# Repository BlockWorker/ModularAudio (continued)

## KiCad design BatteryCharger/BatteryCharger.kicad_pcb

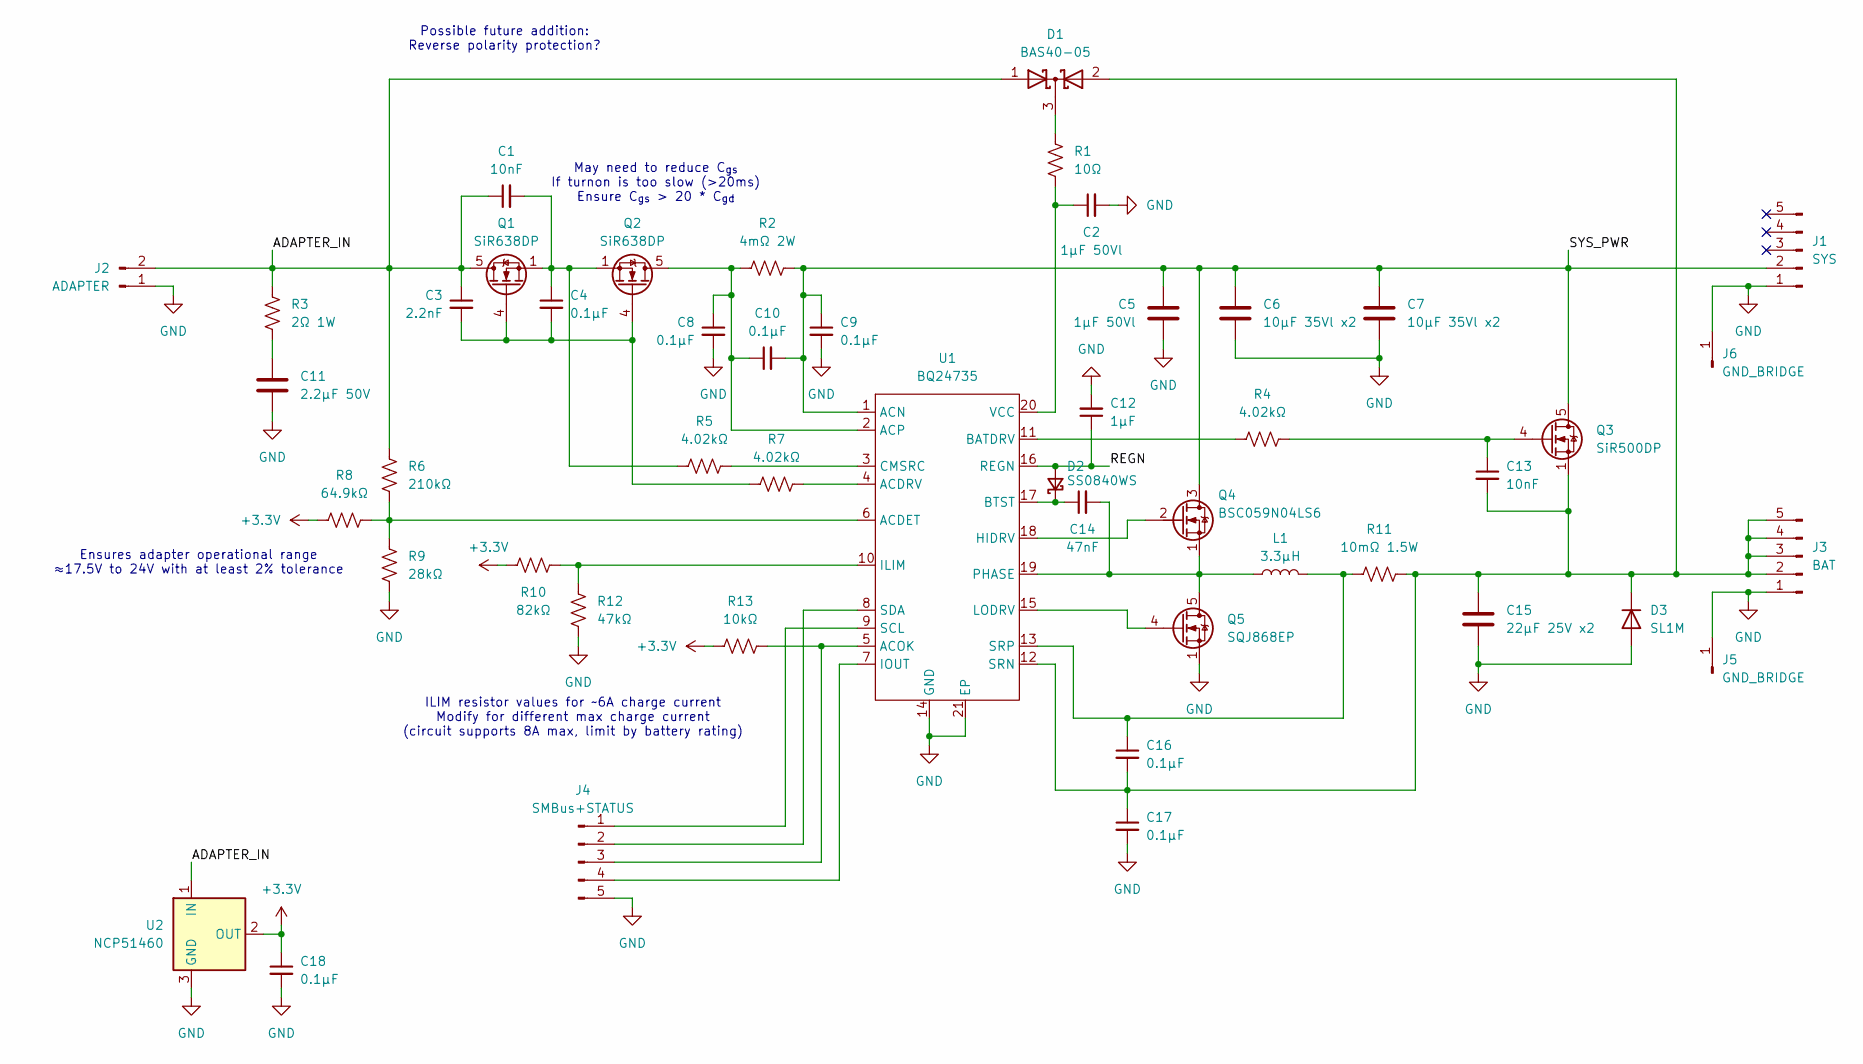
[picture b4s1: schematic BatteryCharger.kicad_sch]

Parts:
C1, C13: 10nF; C_0603_1608Metric
C2, C5: 1µF 50Vl; C_0805_2012Metric
C3: 2.2nF; C_0603_1608Metric
C4, C8, C9, C10, C16, C17, C18: 0.1µF; C_0603_1608Metric
C6, C7: 10µF 35Vl x2; C_1210_3225Metric
C11: 2.2µF 50V; C_0805_2012Metric
C12: 1µF; C_0603_1608Metric
C14: 47nF; C_0603_1608Metric
C15: 22µF 25V x2; C_1210_3225Metric
D1: BAS40-05; SOT-23
D2: SS0840WS; D_SOD-323_HandSoldering
D3: SL1M; D_SOD-123F
J1: SYS; TE_2042274_Solder
J2: ADAPTER; Molex_Mini-Fit_Max_2P_V_215915-1002
J3: BAT; TE_2042274_Solder
J4: SMBus+STATUS; Amphenol_MINITEK_WTB_1.25_5P
J5, J6: GND_BRIDGE; HolePad_2.5mm_3.5mm
L1: 3.3µH; L_Eaton_EXL1V0703
Q1, Q2: SiR638DP; PowerPAK_SO-8_Single
Q3: SiR500DP; PowerPAK_SO-8_Single
Q4: BSC059N04LS6; Infineon_PG-TDSON-8FL_6.15x5.15mm
Q5: SQJ868EP; PowerPAK_SO-8L_Single_Improved
R1: 10Ω; R_0603_1608Metric
R2: 4mΩ 2W; R_0612_1632Metric
R3: 2Ω 1W; R_0508_1220Metric
R4, R5, R7: 4.02kΩ; R_0603_1608Metric
R6: 210kΩ; R_0603_1608Metric
R8: 64.9kΩ; R_0603_1608Metric
R9: 28kΩ; R_0603_1608Metric
R10: 82kΩ; R_0603_1608Metric
R11: 10mΩ 1.5W; R_0612_1632Metric
R12: 47kΩ; R_0603_1608Metric
R13: 10kΩ; R_0603_1608Metric
U1: BQ24735; VQFN-20-1EP_3.5x3.5mm_P0.5mm_EP2.05x2.05mm
U2: NCP51460; SOT-23

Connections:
+3.3V: C18.1, R8.1, R10.1, R13.1, U2.2 (OUT)
/ADAPTER_IN: C1.1, C3.1, D1.1 (A), J2.2, Q1.5 (D), R3.1, R6.1, U2.1 (IN)
/REGN: C12.1, D2.2 (A), U1.16 (REGN)
/SYS_PWR: C5.1, C6.1, C7.1, C9.1, C10.2, J1.2, Q3.5 (D), Q4.3 (D), R2.2, U1.1 (ACN)
GND: C2.2, C5.2, C6.2, C7.2, C8.2, C9.2, C11.2, C12.2, C15.2, C17.2, C18.2, D3.2 (A), J1.1, J2.1, J3.1, J4.5, J5.1, J6.1, Q5.1 (S), Q5.2 (S), Q5.3 (S), R9.2, R12.1, U1.14 (GND), U1.21 (EP), U2.3 (GND)
unnamed: C1.2, C4.1, Q1.1 (S), Q1.2 (S), Q1.3 (S), Q2.1 (S), Q2.2 (S), Q2.3 (S), R5.1
unnamed: C11.1, R3.2
unnamed: D1.3 (K), R1.1
unnamed: C14.1, D2.1 (K), U1.17 (BTST)
unnamed: C13.2, C15.1, C16.2, C17.1, D1.2 (A), D3.1 (K), J3.2, J3.3, J3.4, J3.5, Q3.1 (S), Q3.2 (S), Q3.3 (S), R11.2, U1.12 (SRN)
unnamed: J4.1, U1.9 (SCL)
unnamed: J4.2, U1.8 (SDA)
unnamed: J4.3, R13.2, U1.5 (ACOK)
unnamed: J4.4, U1.7 (IOUT)
unnamed: C3.2, C4.2, Q1.4 (G), Q2.4 (G), R7.1
unnamed: C8.1, C10.1, Q2.5 (D), R2.1, U1.2 (ACP)
unnamed: C13.1, Q3.4 (G), R4.2
unnamed: Q4.2 (G), U1.18 (HIDRV)
unnamed: C14.2, L1.1, Q4.1 (S), Q5.5 (D), U1.19 (PHASE)
unnamed: Q5.4 (G), U1.15 (LODRV)
unnamed: R6.2, R8.2, R9.1, U1.6 (ACDET)
unnamed: R7.2, U1.4 (ACDRV)
unnamed: R4.1, U1.11 (BATDRV)
unnamed: R5.2, U1.3 (CMSRC)
unnamed: R10.2, R12.2, U1.10 (ILIM)
unnamed: C16.1, L1.2, R11.1, U1.13 (SRP)
unnamed: C2.1, R1.2, U1.20 (VCC)

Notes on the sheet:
ILIM resistor values for ~6A charge current Modify for different max charge current (circuit supports 8A max, limit by battery rating)
May need to reduce C_{gs} If turnon is too slow (>20ms) Ensure C_{gs} > 20 * C_{gd}
Possible future addition: Reverse polarity protection?
Ensures adapter operational range ≈17.5V to 24V with at least 2% tolerance

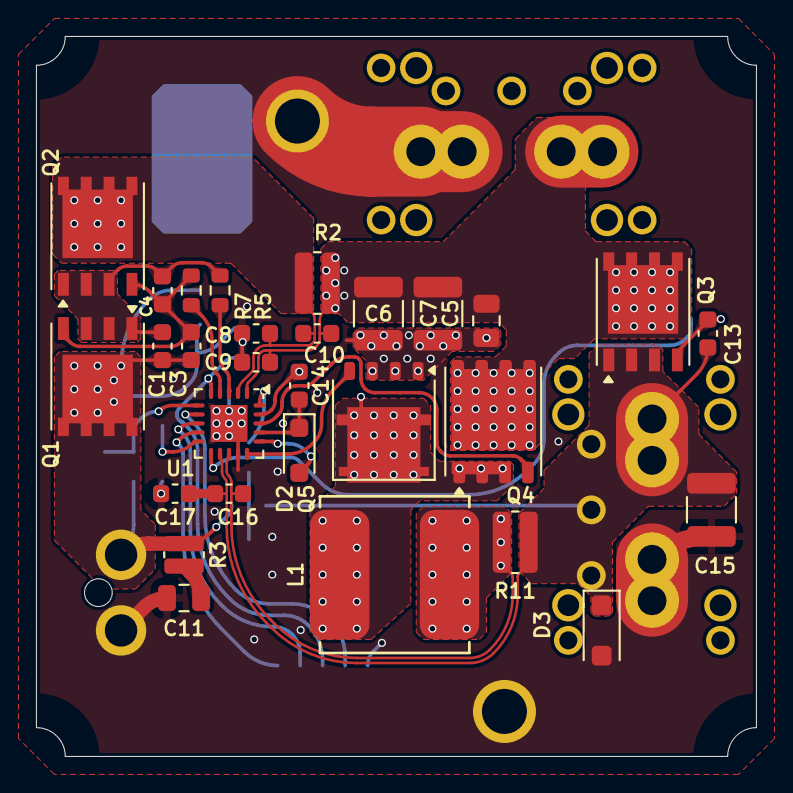
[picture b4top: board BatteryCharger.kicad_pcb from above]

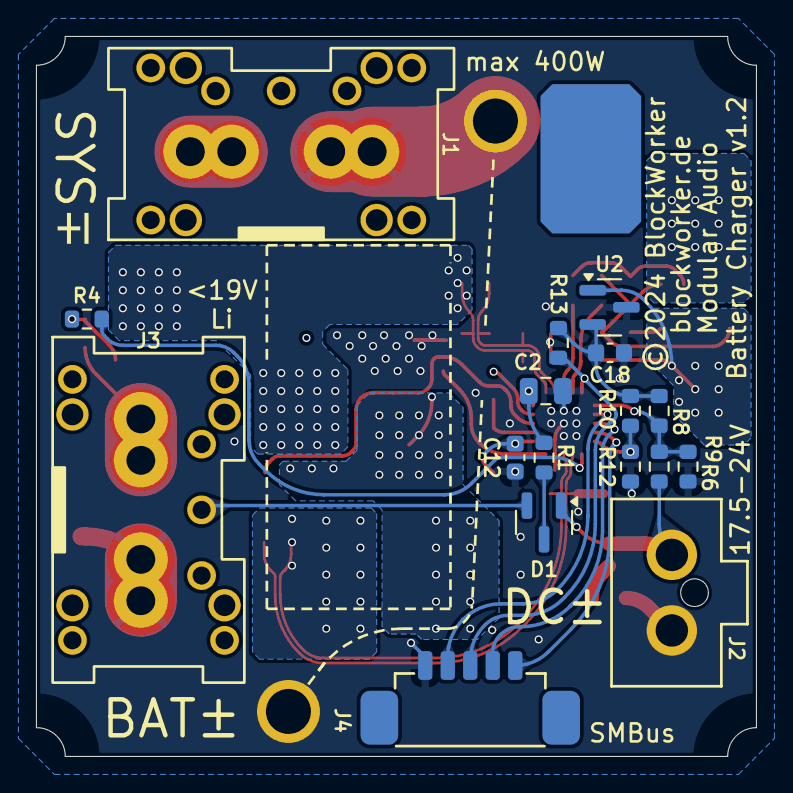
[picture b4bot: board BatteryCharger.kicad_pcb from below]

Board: 4 copper layers, 40.0 x 40.0 mm, 48 parts (17 on the bottom side), 27 nets.

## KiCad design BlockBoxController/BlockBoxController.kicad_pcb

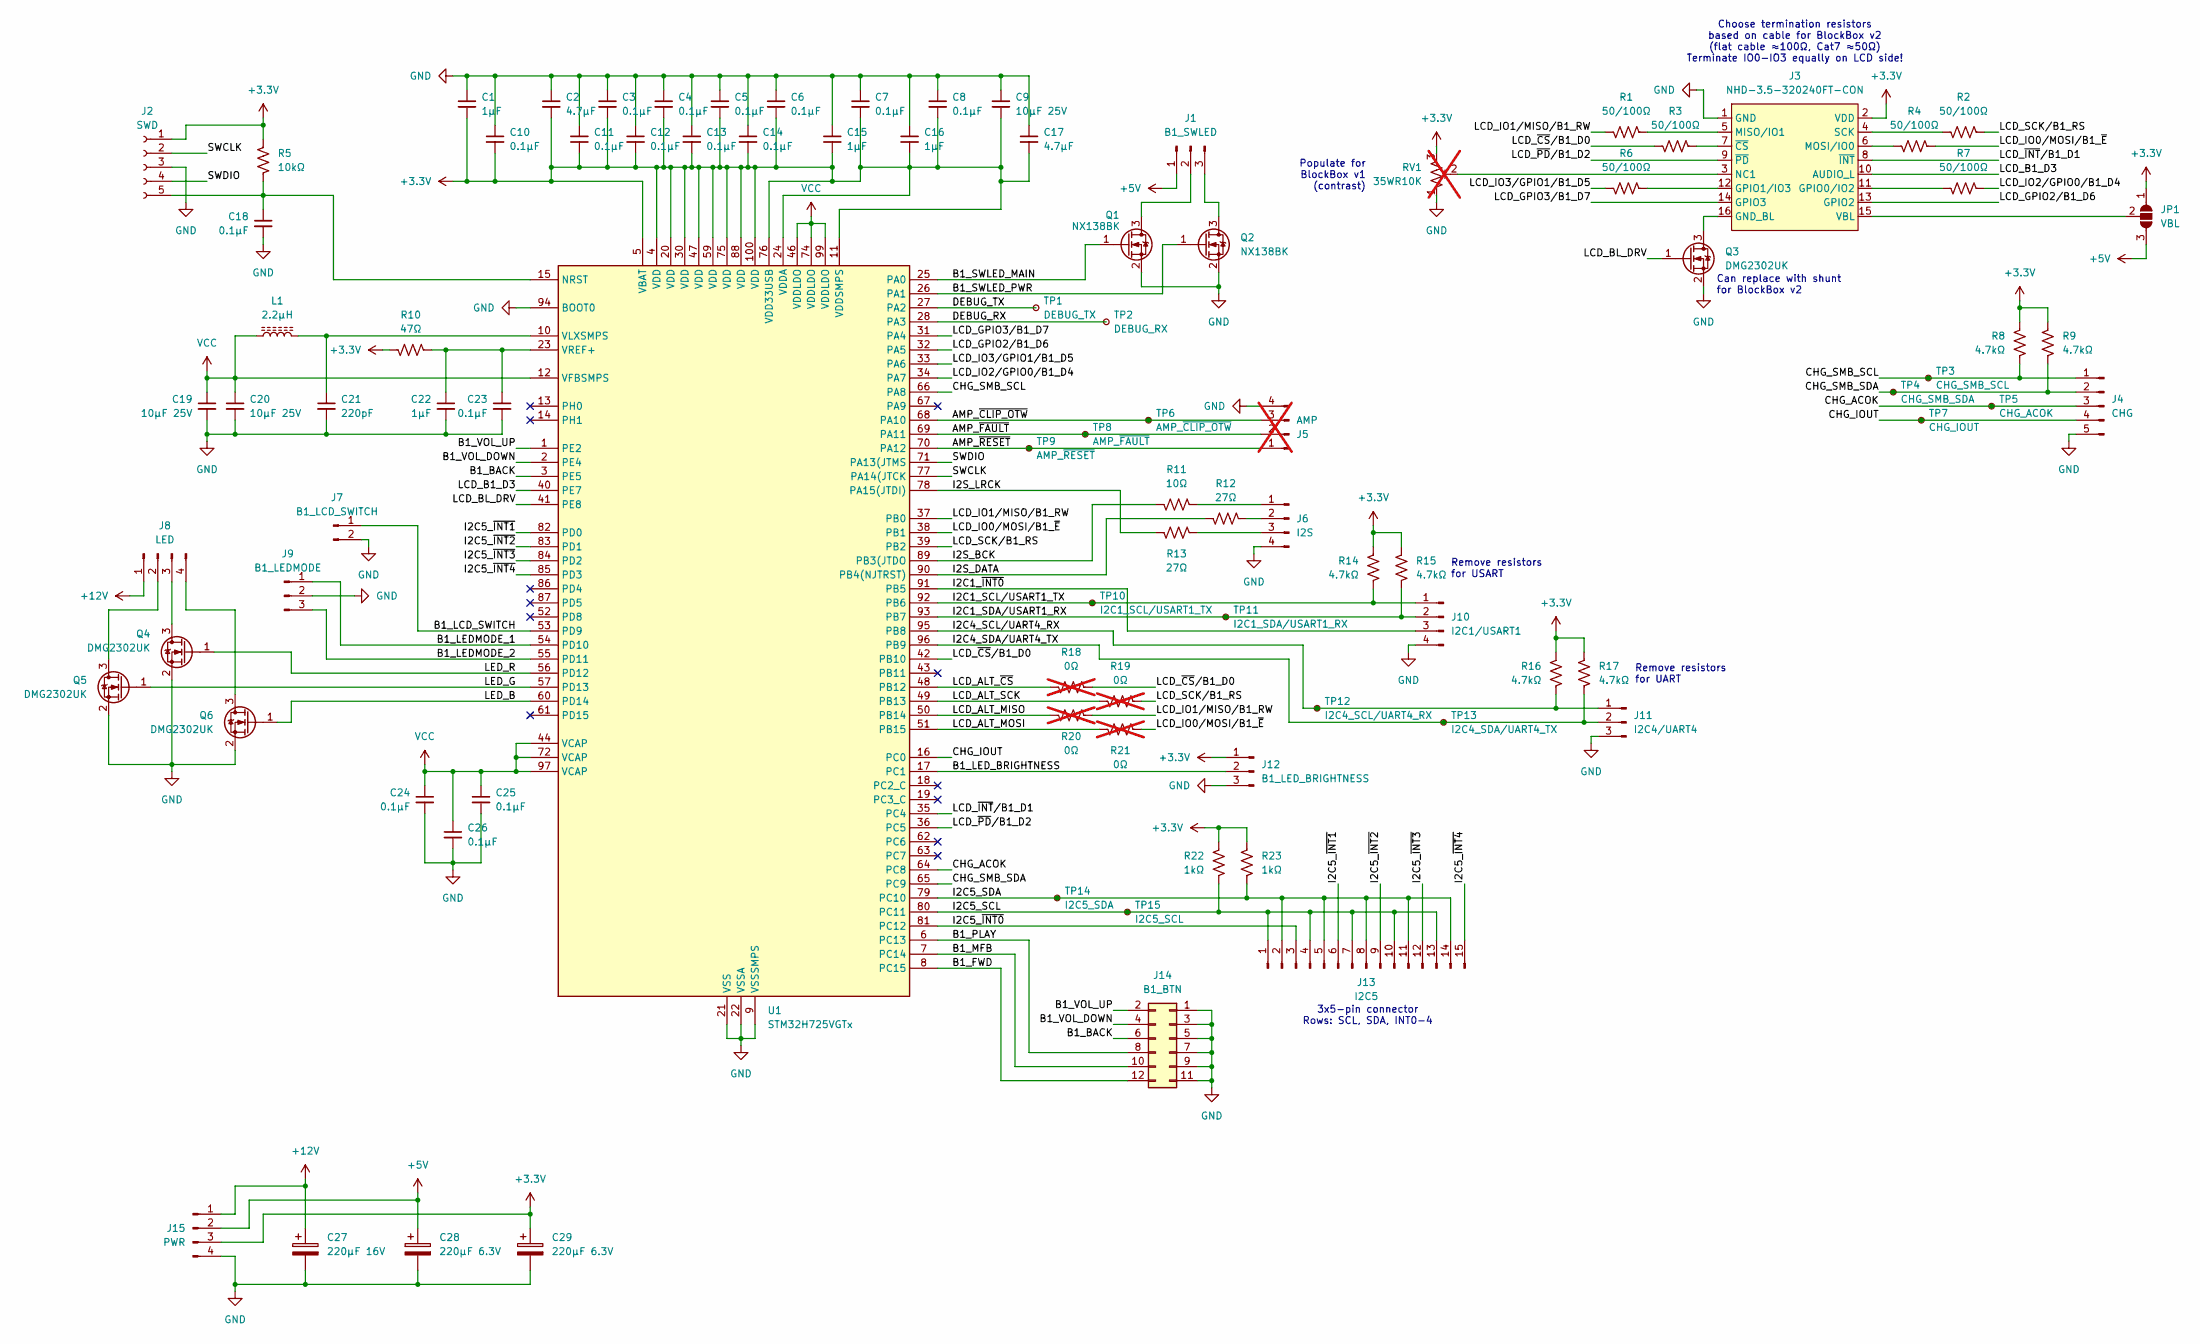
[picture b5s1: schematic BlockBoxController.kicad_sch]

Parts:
C1, C15, C16, C22: 1µF; C_0603_1608Metric
C2, C17: 4.7µF; C_0603_1608Metric
C3, C4, C5, C6, C7, C8, C10, C11, C12, C13, C14, C18, C23, C24, C25, C26: 0.1µF; C_0603_1608Metric
C9, C19, C20: 10µF 25V; C_0805_2012Metric
C21: 220pF; C_0603_1608Metric
C27: 220µF 16V; CP_Elec_6.3x7.7
C28, C29: 220µF 6.3V; CP_Elec_5x5.8
J1: B1_SWLED; PinHeader_1x03_P2.54mm_Vertical
J2: SWD; PinSocket_1x05_P1.27mm_Vertical_SMD_Pin1Right
J3: NHD-3.5-320240FT-CON; PinHeader_2x09_P2.54mm_Vertical_Mirrored
J4: CHG; Amphenol_MINITEK_WTB_1.25_5P
J5: AMP; Amphenol_MINITEK_WTB_1.25_4P; not fitted
J6: I2S; Amphenol_MINITEK_WTB_1.25_4P
J7: B1_LCD_SWITCH; PinHeader_1x02_P2.54mm_Vertical
J8: LED; PinHeader_1x04_P2.54mm_Vertical
J9: B1_LEDMODE; PinHeader_1x03_P2.54mm_Vertical
J10: I2C1/USART1; Amphenol_MINITEK_WTB_1.25_4P
J11: I2C4/UART4; Amphenol_MINITEK_WTB_1.25_3P
J12: B1_LED_BRIGHTNESS; PinHeader_1x03_P2.54mm_Vertical
J13: I2C5; PinHeader_3x05_P2.54mm_Vertical
J14: B1_BTN; PinHeader_2x06_P2.54mm_Vertical
J15: PWR; Molex_Nano-Fit_105309-xx04_1x04_P2.50mm_Vertical
JP1: VBL; SolderJumper-3_P1.3mm_Open_RoundedPad1.0x1.5mm
L1: 2.2µH; L_0805_2012Metric
Q1, Q2: NX138BK; SOT-23
Q3, Q4, Q5, Q6: DMG2302UK; SOT-23
R1, R2, R3, R4, R6, R7: 50/100Ω; R_0603_1608Metric
R5: 10kΩ; R_0603_1608Metric
R8, R9, R14, R15, R16, R17: 4.7kΩ; R_0603_1608Metric
R10: 47Ω; R_0603_1608Metric
R11: 10Ω; R_0603_1608Metric
R12, R13: 27Ω; R_0603_1608Metric
R18, R19, R20, R21: 0Ω; R_0603_1608Metric; not fitted
R22, R23: 1kΩ; R_0603_1608Metric
RV1: 35WR10K; Potentiometer_TT_35W; not fitted
TP1: DEBUG_TX; TP_0603_1608Metric_Fused
TP2: DEBUG_RX; TP_0603_1608Metric_Fused
TP3: CHG_SMB_SCL; TP_0603_1608Metric_Fused
TP4: CHG_SMB_SDA; TP_0603_1608Metric_Fused
TP5: CHG_ACOK; TP_0603_1608Metric_Fused
TP6: AMP_~{CLIP_OTW}; TestPoint_Pad_D1.0mm
TP7: CHG_IOUT; TestPoint_Pad_D1.0mm
TP8: AMP_~{FAULT}; TestPoint_Pad_D1.0mm
TP9: AMP_~{RESET}; TestPoint_Pad_D1.0mm
TP10: I2C1_SCL/USART1_TX; TP_0603_1608Metric_Fused
TP11: I2C1_SDA/USART1_RX; TP_0603_1608Metric_Fused
TP12: I2C4_SCL/UART4_RX; TP_0603_1608Metric_Fused
TP13: I2C4_SDA/UART4_TX; TP_0603_1608Metric_Fused
TP14: I2C5_SDA; TP_0603_1608Metric_Fused
TP15: I2C5_SCL; TP_0603_1608Metric_Fused
U1: STM32H725VGTx; LQFP-100_14x14mm_P0.5mm

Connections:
+3.3V: C1.2, C2.2, C3.2, C4.2, C5.2, C6.2, C7.2, C8.2, C9.2, C10.2, C11.2, C12.2, C13.2, C14.2, C15.2, C16.2, C17.2, C29.1, J2.1, J3.2 (VDD), J12.1, J15.3, JP1.1 (A), R5.1, R8.1, R9.1, R10.1, R14.1, R15.1, R16.1, R17.1, R22.1, R23.1, RV1.3, U1.4 (VDD), U1.5 (VBAT), U1.11 (VDDSMPS), U1.20 (VDD), U1.24 (VDDA), U1.30 (VDD), U1.47 (VDD), U1.59 (VDD), U1.75 (VDD), U1.76 (VDD33USB), U1.88 (VDD), U1.100 (VDD)
+5V: C28.1, J1.1, J15.2, JP1.3 (B)
+12V: C27.1, J8.1, J15.1
/AMP_~CLIP_OTW: J5.3, TP6.1, U1.68 (PA10)
/AMP_~FAULT: J5.2, TP8.1, U1.69 (PA11)
/AMP_~RESET: J5.1, TP9.1, U1.70 (PA12)
/B1_BACK: J14.6, U1.3 (PE5)
/B1_FWD: J14.12, U1.8 (PC15)
/B1_LCD_SWITCH: J7.1, U1.53 (PD9)
/B1_LEDMODE_1: J9.1, U1.54 (PD10)
/B1_LEDMODE_2: J9.3, U1.55 (PD11)
/B1_LED_BRIGHTNESS: J12.2, U1.17 (PC1)
/B1_MFB: J14.10, U1.7 (PC14)
/B1_PLAY: J14.8, U1.6 (PC13)
/B1_SWLED_MAIN: Q1.1 (G), U1.25 (PA0)
/B1_SWLED_PWR: Q2.1 (G), U1.26 (PA1)
/B1_VOL_DOWN: J14.4, U1.2 (PE4)
/B1_VOL_UP: J14.2, U1.1 (PE2)
/CHG_ACOK: J4.3, TP5.1, U1.64 (PC8)
/CHG_IOUT: J4.4, TP7.1, U1.16 (PC0)
/CHG_SMB_SCL: J4.1, R8.2, TP3.1, U1.66 (PA8)
/CHG_SMB_SDA: J4.2, R9.2, TP4.1, U1.65 (PC9)
/DEBUG_RX: TP2.1, U1.28 (PA3)
/DEBUG_TX: TP1.1, U1.27 (PA2)
/I2C1_SCL/USART1_TX: J10.1, R14.2, TP10.1, U1.92 (PB6)
/I2C1_SDA/USART1_RX: J10.2, R15.2, TP11.1, U1.93 (PB7)
/I2C1_~INT0: J10.3, U1.91 (PB5)
/I2C4_SCL/UART4_RX: J11.1, R16.2, TP12.1, U1.95 (PB8)
/I2C4_SDA/UART4_TX: J11.2, R17.2, TP13.1, U1.96 (PB9)
/I2C5_SCL: J13.1, J13.4, J13.7, J13.10, J13.13, R22.2, TP15.1, U1.80 (PC11)
/I2C5_SDA: J13.2, J13.5, J13.8, J13.11, J13.14, R23.2, TP14.1, U1.79 (PC10)
/I2C5_~INT0: J13.3, U1.81 (PC12)
/I2C5_~INT1: J13.6, U1.82 (PD0)
/I2C5_~INT2: J13.9, U1.83 (PD1)
/I2C5_~INT3: J13.12, U1.84 (PD2)
/I2C5_~INT4: J13.15, U1.85 (PD3)
/I2S_BCK: R11.1, U1.89 (PB3(JTDO)
/I2S_DATA: R12.1, U1.90 (PB4(NJTRST))
/I2S_LRCK: R13.1, U1.78 (PA15(JTDI))
/LCD_ALT_MISO: R20.1, U1.50 (PB14)
/LCD_ALT_MOSI: R21.1, U1.51 (PB15)
/LCD_ALT_SCK: R19.1, U1.49 (PB13)
/LCD_ALT_~CS: R18.1, U1.48 (PB12)
/LCD_B1_D3: J3.10 (AUDIO_L), U1.40 (PE7)
/LCD_BL_DRV: Q3.1 (G), U1.41 (PE8)
/LCD_GPIO2/B1_D6: J3.13 (GPIO2), U1.32 (PA5)
/LCD_GPIO3/B1_D7: J3.14 (GPIO3), U1.31 (PA4)
/LCD_IO0/MOSI/B1_~E: R4.2, R21.2, U1.38 (PB1)
/LCD_IO1/MISO/B1_RW: R1.1, R20.2, U1.37 (PB0)
/LCD_IO2/GPIO0/B1_D4: R7.2, U1.34 (PA7)
/LCD_IO3/GPIO1/B1_D5: R6.1, U1.33 (PA6)
/LCD_SCK/B1_RS: R2.2, R19.2, U1.39 (PB2)
/LCD_~CS/B1_D0: R3.1, R18.2, U1.42 (PB10)
/LCD_~INT/B1_D1: J3.8 (~INT), U1.35 (PC4)
/LCD_~PD/B1_D2: J3.9 (~PD), U1.36 (PC5)
/LED_B: Q6.1 (G), U1.60 (PD14)
/LED_G: Q5.1 (G), U1.57 (PD13)
/LED_R: Q4.1 (G), U1.56 (PD12)
/SWCLK: J2.2, U1.77 (PA14(JTCK)
/SWDIO: J2.4, U1.71 (PA13(JTMS)
GND: C1.1, C2.1, C3.1, C4.1, C5.1, C6.1, C7.1, C8.1, C9.1, C10.1, C11.1, C12.1, C13.1, C14.1, C15.1, C16.1, C17.1, C18.2, C19.2, C20.2, C21.2, C22.2, C23.2, C24.2, C25.2, C26.2, C27.2, C28.2, C29.2, J2.3, J3.1 (GND), J4.5, J5.4, J6.4, J7.2, J9.2, J10.4, J11.3, J12.3, J14.1, J14.3, J14.5, J14.7, J14.9, J14.11, J15.4, Q1.2 (S), Q2.2 (S), Q3.2 (S), Q4.2 (S), Q5.2 (S), Q6.2 (S), RV1.1, U1.9 (VSSSMPS), U1.21 (VSS), U1.22 (VSSA), U1.29 (VSS), U1.45 (VSS), U1.58 (VSS), U1.73 (VSS), U1.94 (BOOT0), U1.98 (VSS)
unnamed: J1.2, Q1.3 (D)
unnamed: J1.3, Q2.3 (D)
unnamed: C18.1, J2.5, R5.2, U1.15 (NRST)
unnamed: J3.11 (GPIO0/IO2), R7.1
unnamed: J3.12 (GPIO1/IO3), R6.2
unnamed: J3.5 (MISO/IO1), R1.2
unnamed: J3.6 (MOSI/IO0), R4.1
unnamed: J3.3 (NC1), RV1.2
unnamed: J3.4 (SCK), R2.1
unnamed: J3.7 (~CS), R3.2
unnamed: J6.1, R11.2
unnamed: J6.2, R12.2
unnamed: J6.3, R13.2
unnamed: J8.2, Q5.3 (D)
unnamed: J8.3, Q4.3 (D)
unnamed: J8.4, Q6.3 (D)
unnamed: J3.15 (VBL), J3.17 (VBL), JP1.2 (C)
unnamed: J3.16 (GND_BL), J3.18 (GND_BL), Q3.3 (D)
unnamed: C21.1, L1.2, U1.10 (VLXSMPS)
unnamed: C22.1, C23.1, R10.2, U1.23 (VREF+)
VCC: C19.1, C20.1, C24.1, C25.1, C26.1, L1.1, U1.12 (VFBSMPS), U1.44 (VCAP), U1.46 (VDDLDO), U1.72 (VCAP), U1.74 (VDDLDO), U1.97 (VCAP), U1.99 (VDDLDO)

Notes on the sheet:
Can replace with shunt for BlockBox v2
3x5-pin connector Rows: SCL, SDA, INT0-4
Remove resistors for UART
Populate for BlockBox v1 (contrast)
Choose termination resistors based on cable for BlockBox v2 (flat cable ≈100Ω, Cat7 ≈50Ω) Terminate IO0-IO3 equally on LCD side!
Remove resistors for USART

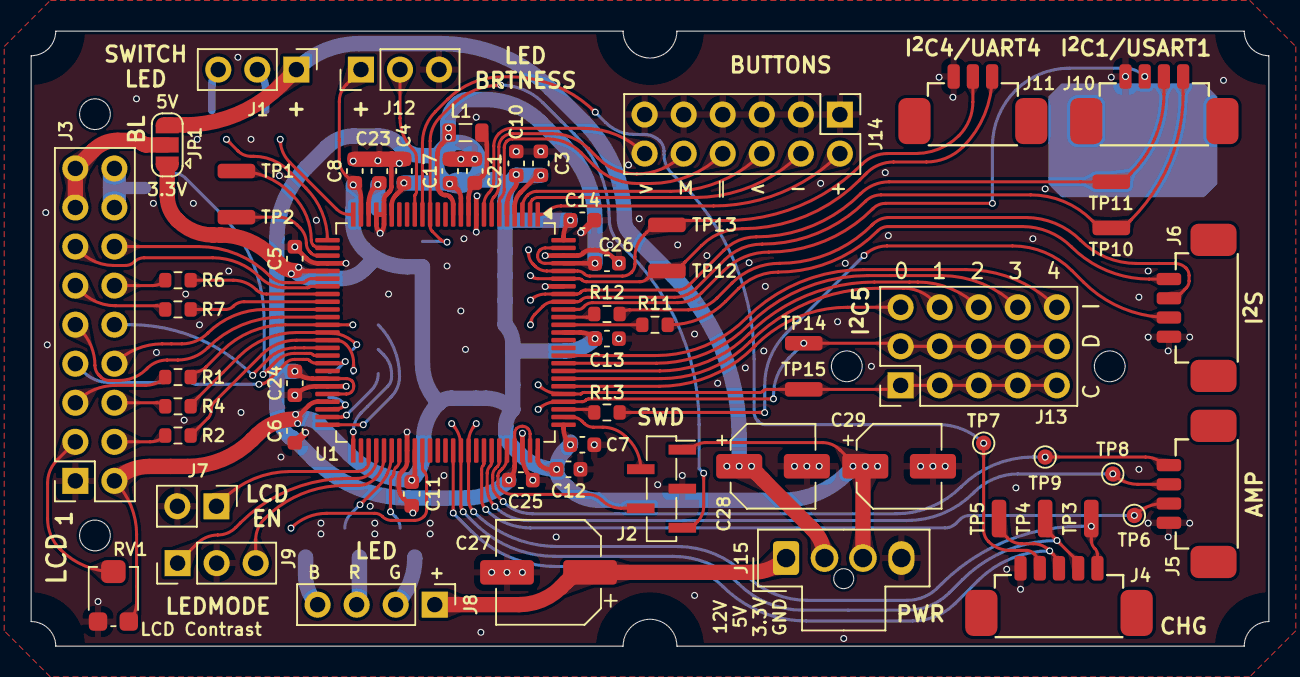
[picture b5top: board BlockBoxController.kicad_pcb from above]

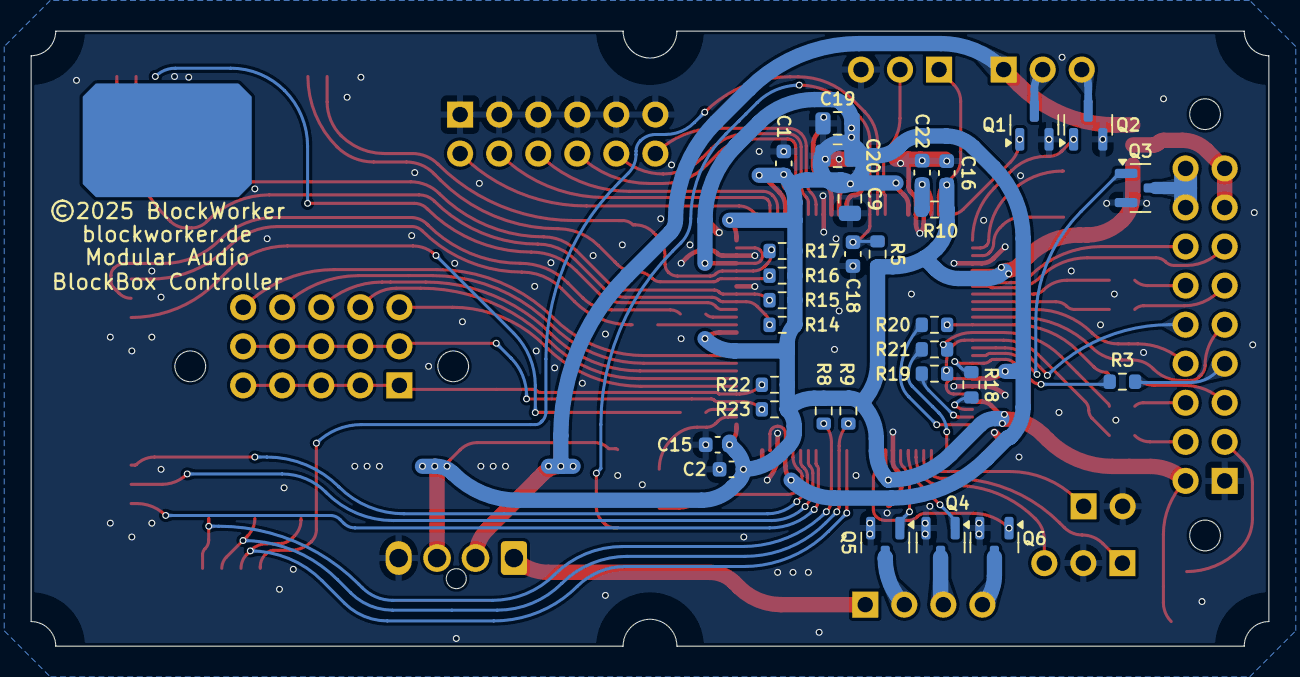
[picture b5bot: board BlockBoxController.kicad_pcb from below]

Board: 4 copper layers, 80.5 x 40.0 mm, 92 parts (30 on the bottom side), 82 nets.

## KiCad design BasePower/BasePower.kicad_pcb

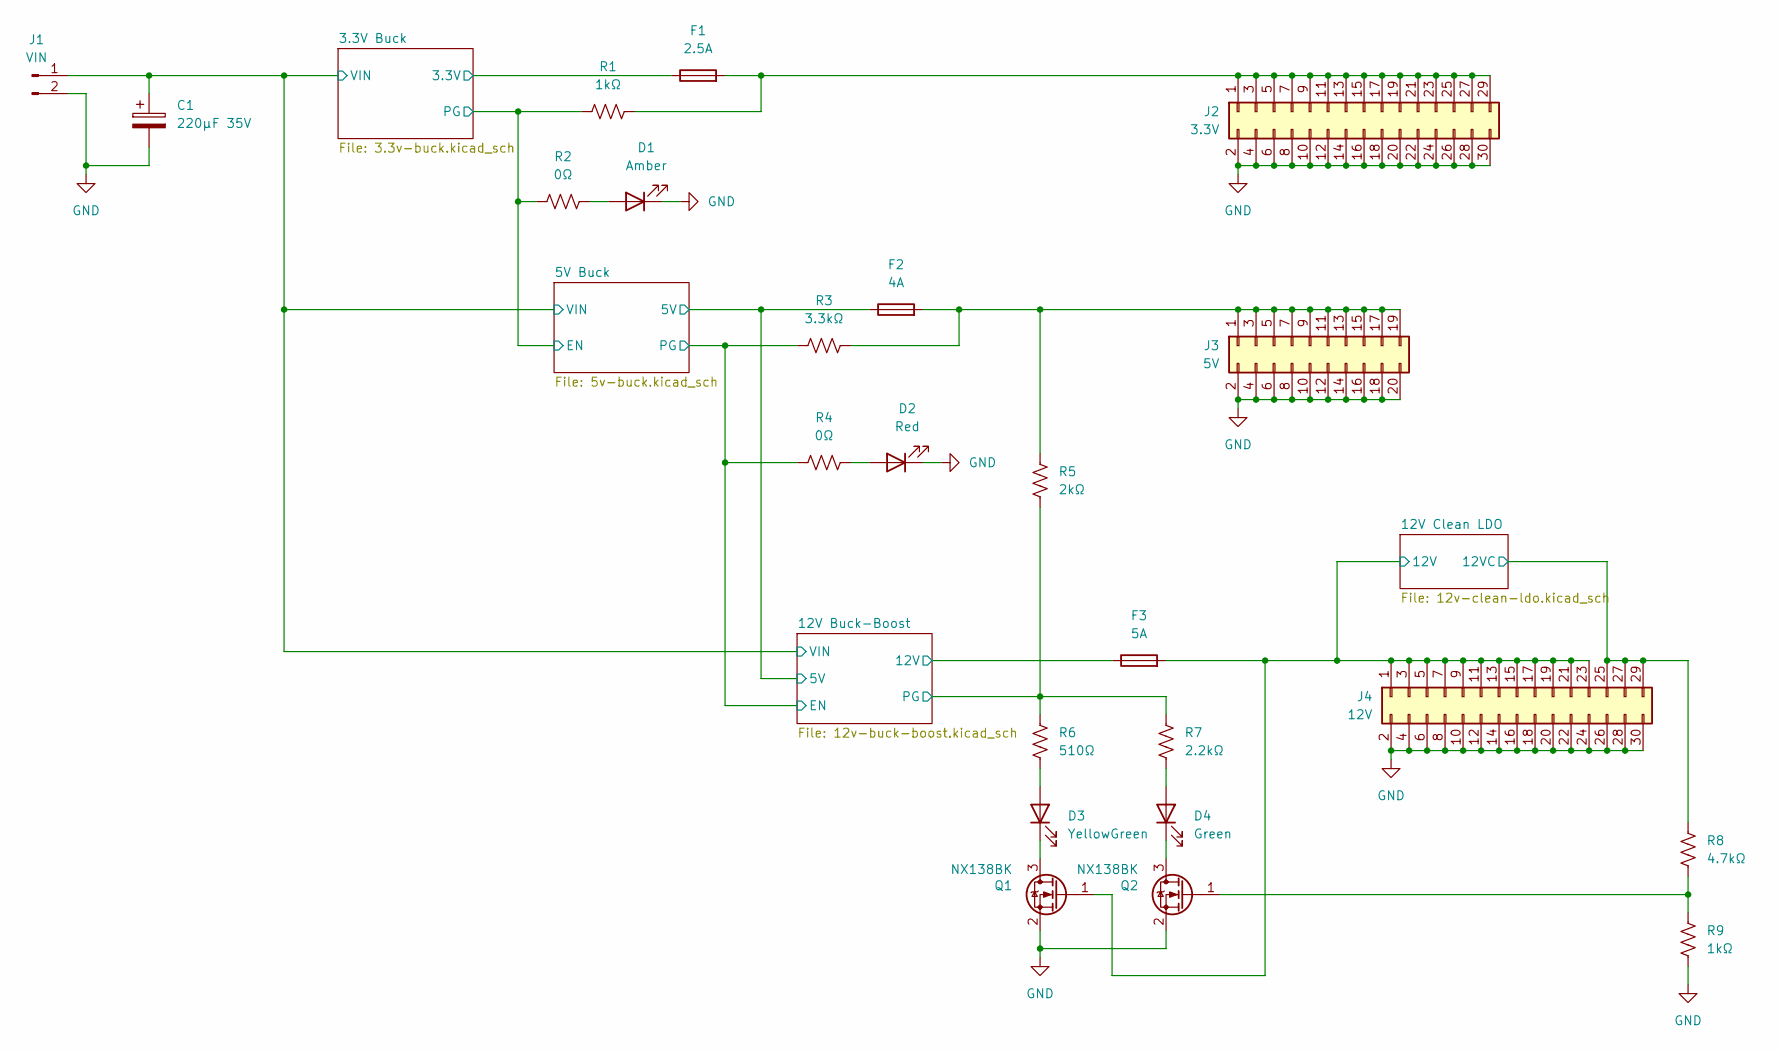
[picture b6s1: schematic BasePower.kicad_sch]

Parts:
C1: 220µF 35V; CP_Radial_D8.0mm_P3.50mm
D1: Amber; LED_0603_1608Metric
D2: Red; LED_0603_1608Metric
D3: YellowGreen; LED_0603_1608Metric
D4: Green; LED_0603_1608Metric
F1: 2.5A; Fuse_0603_1608Metric
F2: 4A; Fuse_0603_1608Metric
F3: 5A; Fuse_0603_1608Metric
J1: VIN; Molex_Nano-Fit_105309-xx02_1x02_P2.50mm_Vertical
J2: 3.3V; PinHeader_2x15_P2.54mm_Vertical
J3: 5V; PinHeader_2x10_P2.54mm_Vertical
J4: 12V; PinHeader_2x15_P2.54mm_Vertical
Q1, Q2: NX138BK; SOT-23
R1, R9: 1kΩ; R_0603_1608Metric
R2, R4: 0Ω; R_0603_1608Metric
R3: 3.3kΩ; R_0603_1608Metric
R5: 2kΩ; R_0603_1608Metric
R6: 510Ω; R_0603_1608Metric
R7: 2.2kΩ; R_0603_1608Metric
R8: 4.7kΩ; R_0603_1608Metric

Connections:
/3.3V Buck/3.3V: F1.1; also elsewhere on the board
/3.3V Buck/PG: R1.1, R2.1; also elsewhere on the board
/12V Buck-Boost/5V: F2.1; also elsewhere on the board
/12V Buck-Boost/12V: F3.1; also elsewhere on the board
/12V Buck-Boost/EN: R3.1, R4.1; also elsewhere on the board
/12V Buck-Boost/PG: R5.1, R6.1, R7.1; also elsewhere on the board
/12V Buck-Boost/VIN: C1.1, J1.1; also elsewhere on the board
/12V Clean LDO/12V: F3.2, J4.1, J4.3, J4.5, J4.7, J4.9, J4.11, J4.13, J4.15, J4.17, J4.19, J4.21, J4.23, Q1.1 (G); also elsewhere on the board
/12V Clean LDO/12VC: J4.25, J4.27, J4.29, R8.1; also elsewhere on the board
GND: C1.2, D1.1 (K), D2.1 (K), J1.2, J2.2, J2.4, J2.6, J2.8, J2.10, J2.12, J2.14, J2.16, J2.18, J2.20, J2.22, J2.24, J2.26, J2.28, J2.30, J3.2, J3.4, J3.6, J3.8, J3.10, J3.12, J3.14, J3.16, J3.18, J3.20, J4.2, J4.4, J4.6, J4.8, J4.10, J4.12, J4.14, J4.16, J4.18, J4.20, J4.22, J4.24, J4.26, J4.28, J4.30, Q1.2 (S), Q2.2 (S), R9.2; also elsewhere on the board
unnamed: D1.2 (A), R2.2
unnamed: D2.2 (A), R4.2
unnamed: D3.2 (A), R6.2
unnamed: D3.1 (K), Q1.3 (D)
unnamed: D4.2 (A), R7.2
unnamed: D4.1 (K), Q2.3 (D)
unnamed: F1.2, J2.1, J2.3, J2.5, J2.7, J2.9, J2.11, J2.13, J2.15, J2.17, J2.19, J2.21, J2.23, J2.25, J2.27, J2.29, R1.2
unnamed: F2.2, J3.1, J3.3, J3.5, J3.7, J3.9, J3.11, J3.13, J3.15, J3.17, J3.19, R3.2, R5.2
unnamed: Q2.1 (G), R8.2, R9.1

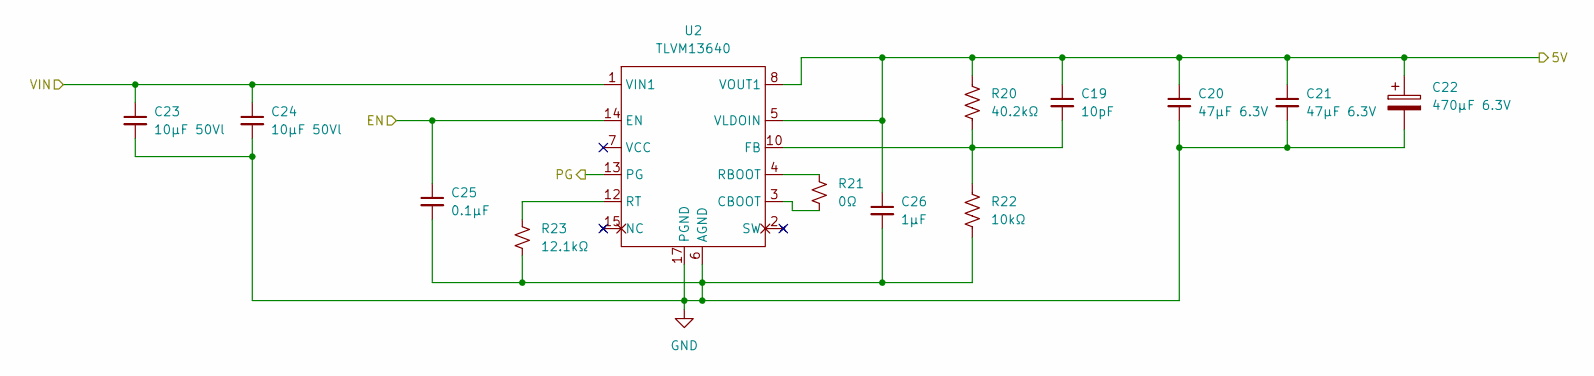
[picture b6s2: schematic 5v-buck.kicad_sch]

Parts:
C19: 10pF; C_0603_1608Metric
C20, C21: 47µF 6.3V; C_1210_3225Metric
C22: 470µF 6.3V; CP_Radial_D6.3mm_P2.50mm
C23, C24: 10µF 50Vl; C_1210_3225Metric
C25: 0.1µF; C_0603_1608Metric
C26: 1µF; C_0603_1608Metric
R20: 40.2kΩ; R_0603_1608Metric
R21: 0Ω; R_0603_1608Metric
R22: 10kΩ; R_0603_1608Metric
R23: 12.1kΩ; R_0603_1608Metric
U2: TLVM13640; TI_B3QFN-20

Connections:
/3.3V Buck/PG: C25.1, U2.14 (EN); also elsewhere on the board
/12V Buck-Boost/5V: C19.1, C20.1, C21.1, C22.1, C26.1, R20.1, U2.5 (VLDOIN), U2.8 (VOUT1), U2.9 (VOUT2); also elsewhere on the board
/12V Buck-Boost/EN: U2.13 (PG); also elsewhere on the board
/12V Buck-Boost/VIN: C23.1, C24.1, U2.1 (VIN1), U2.16 (VIN2); also elsewhere on the board
GND: C20.2, C21.2, C22.2, C23.2, C24.2, C25.2, C26.2, R22.2, R23.2, U2.6 (AGND), U2.11 (AGND), U2.17 (PGND), U2.18 (PGND), U2.19 (PGND), U2.20 (PGND); also elsewhere on the board
unnamed: R21.2, U2.3 (CBOOT)
unnamed: C19.2, R20.2, R22.1, U2.10 (FB)
unnamed: R21.1, U2.4 (RBOOT)
unnamed: R23.1, U2.12 (RT)

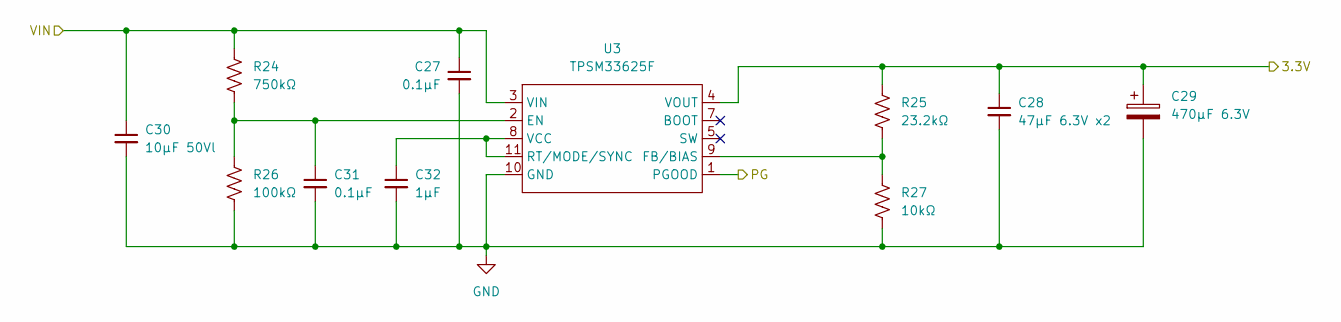
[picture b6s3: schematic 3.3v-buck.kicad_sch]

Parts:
C27, C31: 0.1µF; C_0603_1608Metric
C28: 47µF 6.3V x2; C_1210_3225Metric
C29: 470µF 6.3V; CP_Radial_D6.3mm_P2.50mm
C30: 10µF 50Vl; C_1210_3225Metric
C32: 1µF; C_0603_1608Metric
R24: 750kΩ; R_0603_1608Metric
R25: 23.2kΩ; R_0603_1608Metric
R26: 100kΩ; R_0603_1608Metric
R27: 10kΩ; R_0603_1608Metric
U3: TPSM33625F; TI_QFN-FCMOD-HR

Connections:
/3.3V Buck/3.3V: C28.1, C29.1, R25.1, U3.4 (VOUT); also elsewhere on the board
/3.3V Buck/PG: U3.1 (PGOOD); also elsewhere on the board
/12V Buck-Boost/VIN: C27.1, C30.1, R24.1, U3.3 (VIN); also elsewhere on the board
GND: C27.2, C28.2, C29.2, C30.2, C31.2, C32.2, R26.2, R27.2, U3.10 (GND); also elsewhere on the board
unnamed: C31.1, R24.2, R26.1, U3.2 (EN)
unnamed: R25.2, R27.1, U3.9 (FB/BIAS)
unnamed: C32.1, U3.8 (VCC), U3.11 (RT/MODE/SYNC)

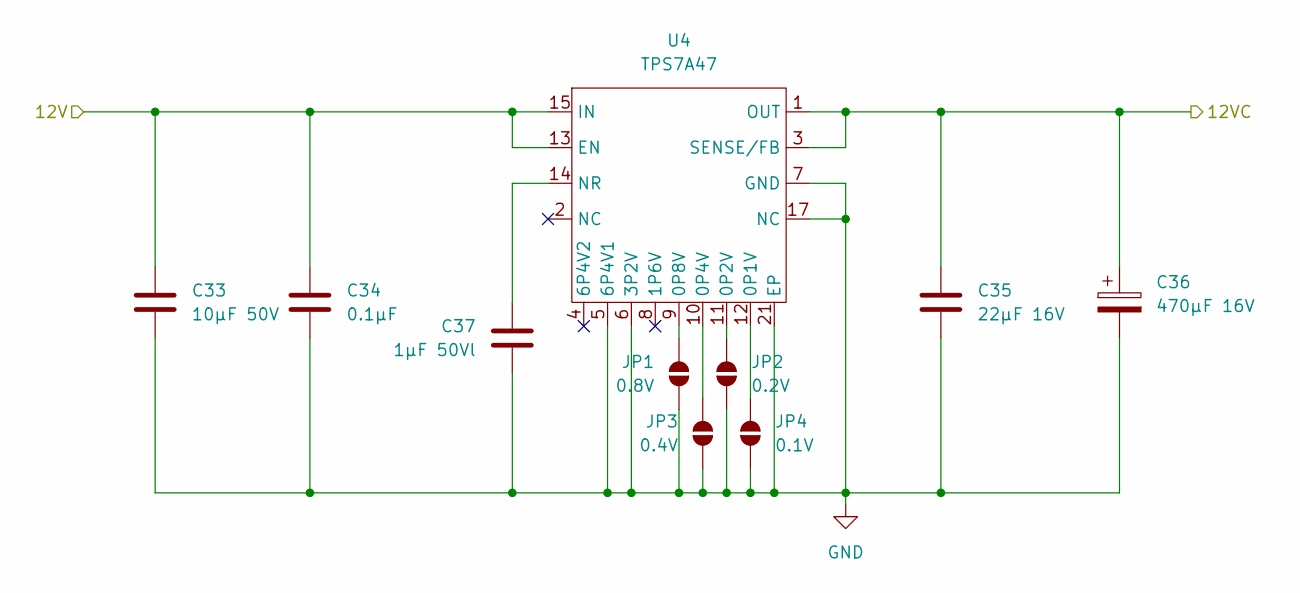
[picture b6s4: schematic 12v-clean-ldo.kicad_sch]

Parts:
C33: 10µF 50V; C_1206_3216Metric
C34: 0.1µF; C_0603_1608Metric
C35: 22µF 16V; C_1210_3225Metric
C36: 470µF 16V; CP_Radial_D6.3mm_P2.50mm
C37: 1µF 50Vl; C_0805_2012Metric
JP1: 0.8V; SolderJumper-2_P1.3mm_Open_RoundedPad1.0x1.5mm
JP2: 0.2V; SolderJumper-2_P1.3mm_Open_RoundedPad1.0x1.5mm
JP3: 0.4V; SolderJumper-2_P1.3mm_Open_RoundedPad1.0x1.5mm
JP4: 0.1V; SolderJumper-2_P1.3mm_Open_RoundedPad1.0x1.5mm
U4: TPS7A47; Texas_RGW0020A_VQFN-20-1EP_5x5mm_P0.65mm_EP3.15x3.15mm

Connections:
/12V Clean LDO/12V: C33.1, C34.1, U4.13 (EN), U4.15 (IN), U4.16 (IN); also elsewhere on the board
/12V Clean LDO/12VC: C35.1, C36.1, U4.1 (OUT), U4.3 (SENSE/FB), U4.20 (OUT); also elsewhere on the board
GND: C33.2, C34.2, C35.2, C36.2, C37.2, JP1.1 (A), JP2.1 (A), JP3.1 (A), JP4.1 (A), U4.5 (6P4V1), U4.6 (3P2V), U4.7 (GND), U4.17 (NC), U4.18 (NC), U4.19 (NC), U4.21 (EP); also elsewhere on the board
unnamed: JP1.2 (B), U4.9 (0P8V)
unnamed: JP2.2 (B), U4.11 (0P2V)
unnamed: JP3.2 (B), U4.10 (0P4V)
unnamed: JP4.2 (B), U4.12 (0P1V)
unnamed: C37.1, U4.14 (NR)

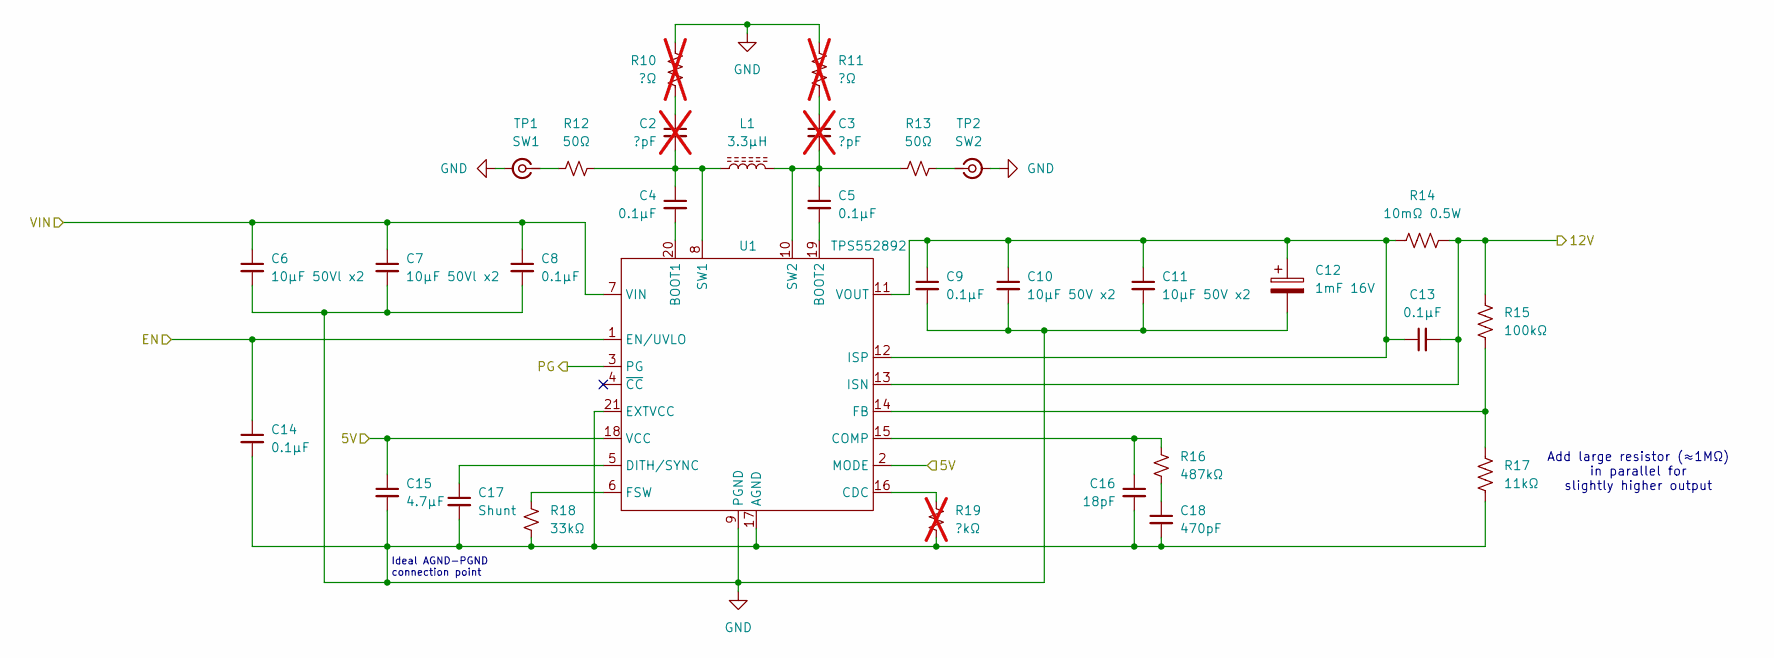
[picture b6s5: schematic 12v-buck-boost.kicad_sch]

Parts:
C2, C3: ?pF; C_0603_1608Metric; not fitted
C4, C5, C8, C9, C13, C14: 0.1µF; C_0603_1608Metric
C6, C7: 10µF 50Vl x2; C_1210_3225Metric
C10, C11: 10µF 50V x2; C_1206_3216Metric
C12: 1mF 16V; CP_Radial_D8.0mm_P3.50mm
C15: 4.7µF; C_0603_1608Metric
C16: 18pF; C_0603_1608Metric
C17: Shunt; C_0603_1608Metric
C18: 470pF; C_0603_1608Metric
L1: 3.3µH; L_Vishay_IHLP-2525
R10, R11: ?Ω; R_1206_3216Metric; not fitted
R12, R13: 50Ω; R_0603_1608Metric
R14: 10mΩ 0.5W; R_0805_2012Metric
R15: 100kΩ; R_0603_1608Metric
R16: 487kΩ; R_0603_1608Metric
R17: 11kΩ; R_0603_1608Metric
R18: 33kΩ; R_0603_1608Metric
R19: ?kΩ; R_0603_1608Metric; not fitted
TP1: SW1; U.FL_Molex_MCRF_73412-0110_Vertical
TP2: SW2; U.FL_Molex_MCRF_73412-0110_Vertical
U1: TPS552892; TI_VQFN-HR-21

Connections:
/12V Buck-Boost/5V: C15.1, U1.2 (MODE), U1.18 (VCC); also elsewhere on the board
/12V Buck-Boost/12V: C13.2, R14.2, R15.1, U1.13 (ISN); also elsewhere on the board
/12V Buck-Boost/EN: C14.1, U1.1 (EN/UVLO); also elsewhere on the board
/12V Buck-Boost/PG: U1.3 (PG); also elsewhere on the board
/12V Buck-Boost/VIN: C6.1, C7.1, C8.1, U1.7 (VIN); also elsewhere on the board
GND: C6.2, C7.2, C8.2, C9.2, C10.2, C11.2, C12.2, C14.2, C15.2, C16.2, C17.2, C18.2, R10.1, R11.1, R17.2, R18.2, R19.2, TP1.2 (Ext), TP2.2 (Ext), U1.9 (PGND), U1.17 (AGND), U1.21 (EXTVCC); also elsewhere on the board
unnamed: C2.1, R10.2
unnamed: C3.1, R11.2
unnamed: C18.1, R16.2
unnamed: R12.2, TP1.1 (In)
unnamed: R13.2, TP2.1 (In)
unnamed: C4.2, U1.20 (BOOT1)
unnamed: C5.2, U1.19 (BOOT2)
unnamed: R19.1, U1.16 (CDC)
unnamed: C16.1, R16.1, U1.15 (COMP)
unnamed: C17.1, U1.5 (DITH/SYNC)
unnamed: R15.2, R17.1, U1.14 (FB)
unnamed: R18.1, U1.6 (FSW)
unnamed: C9.1, C10.1, C11.1, C12.1, C13.1, R14.1, U1.11 (VOUT), U1.12 (ISP)
unnamed: C2.2, C4.1, L1.1, R12.1, U1.8 (SW1)
unnamed: C3.2, C5.1, L1.2, R13.1, U1.10 (SW2)

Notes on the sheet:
Add large resistor (≈1MΩ) in parallel for slightly higher output
Ideal AGND-PGND connection point
